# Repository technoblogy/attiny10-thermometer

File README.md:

# ATtiny10 Thermometer
A small battery-powered thermometer based on an ATtiny10 and a DS18B20 temperature sensor that displays the temperature as a series of red and green flashes in binary on a bi-colour LED. See http://www.technoblogy.com/show?2GPX.

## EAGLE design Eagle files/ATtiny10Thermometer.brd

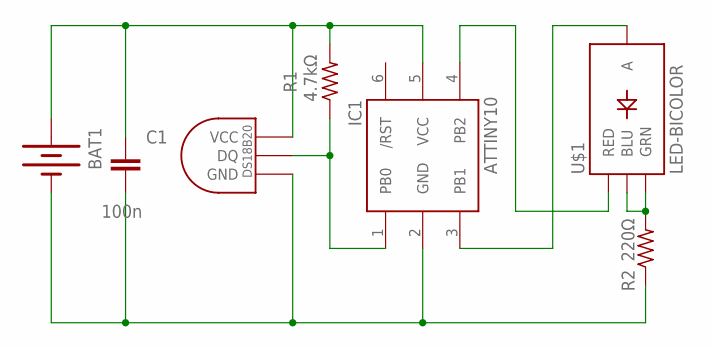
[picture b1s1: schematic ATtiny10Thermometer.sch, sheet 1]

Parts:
BAT1: BATTERY12MM; BATTCON_12MM
C1: 100n; 0603-CAP
IC1: ATTINY10; SOT23-6
R1: 4.7kΩ; R0805
R2: 220Ω; R0805
U$1: LED-BICOLOR; LED-TRICOLOR-SMD
U$2: DS1820; µSOP8

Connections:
unnamed: BAT1.PWR@1 (+), C1.1, IC1.5 (VCC), R1.2, U$2.8 (VCC)
unnamed: IC1.1 (PB0), R1.1, U$2.1 (DQ)
unnamed: R2.2, U$1.B (BLU), U$1.G (GRN)
unnamed: IC1.4 (PB2), U$1.R (RED)
unnamed: IC1.3 (PB1), U$1.A
unnamed: BAT1.GND (-), C1.2, IC1.2 (GND), R2.1, U$2.4 (GND)

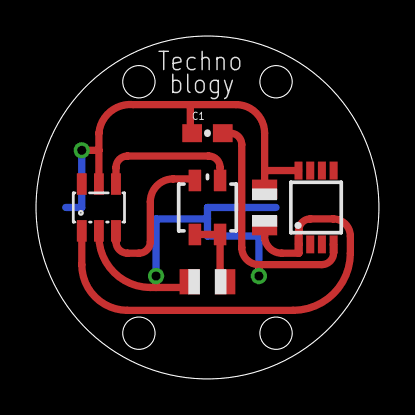
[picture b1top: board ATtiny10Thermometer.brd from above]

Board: 2 copper layers, 19.1 x 19.1 mm, 7 parts (1 on the bottom side), 6 nets.

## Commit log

2019-02-02 Version 1 - 24th January 2019
2019-02-02 Version 1 - 2nd February 2019
2021-03-07 Version 2 - 7th March 2021

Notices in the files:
parts and their libraries:
SparkFun-Capacitors: Licensing: CC v3.0 Share-Alike You are welcome to use this library for commercial purposes.
SparkFun-Electromechanical: Licensing: Creative Commons ShareAlike 4.0 International - https://creativecommons.org/licenses/by-sa/4.0
